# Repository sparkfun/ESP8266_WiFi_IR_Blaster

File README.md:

SparkFun WiFi IR Blaster (ESP8266)
========================================

[*SparkFun ESP8266 WiFi IR Blaster (DEV-15031)*](https://www.sparkfun.com/products/15031)

The WiFi IR Blaster is designed to connect all of your old, legacy IR-controlled devices to a WiFi network -- exposing them to a new method of control. Want to control your TV via a web-browser? Want to ask Alexa to mute your stereo? Want to schedule triggers to your IR-controlled LED strip? These are all applications that the WiFi IR Blaster is perfect for.

The WiFi IR Blaster combines an ESP8266 -- a powerful WiFi/microcontroller SoC -- with an IR emitter and receiver. With built-in WiFi support, the ESP8266 can be programmed to provide an interface between HTTP, MQTT, TCP, and UDP services and infrared-controlled devices.

This product includes the WiFi IR Blaster, a [Lite-ON LTE-302](https://www.sparkfun.com/datasheets/Components/LTE-302.pdf) infrared emitter, and a [TSOP38238 IR receiver](https://www.sparkfun.com/products/10266). The IR emitter and detector are not populated on the board -- allowing you to assemble them in any orientation your project requires.

For help getting started, check out our [WiFi IR Blaster Hookup Guide](https://learn.sparkfun.com/tutorials/wifi-ir-blaster-hookup-guide), which explains how to assemble the board, program it, and use the [IRremoteESP8266](https://github.com/markszabo/IRremoteESP8266) Arduino library.

SparkFun labored with love to create this code. Feel like supporting open source hardware? 
Buy a [breakout board](https://www.sparkfun.com/products/15000) from SparkFun!

Repository Contents
-------------------

* **/Documents** - Datasheets
* **/Hardware** - Eagle design files (.brd, .sch)
* **/Production** - Production panel files (.brd)

Documentation
--------------

* **[Hookup Guide](https://learn.sparkfun.com/tutorials/sparkfun-wifi-ir-blaster-hookup-guide)** - Basic hookup guide.

License Information
-------------------

This product is _**open source**_! 

If you have any questions or concerns on licensing, please contact techsupport@sparkfun.com.

Please use, reuse, and modify these files as you see fit. Please maintain attribution to SparkFun Electronics and release any derivative under the same license.

Distributed as-is; no warranty is given.

- Your friends at SparkFun.

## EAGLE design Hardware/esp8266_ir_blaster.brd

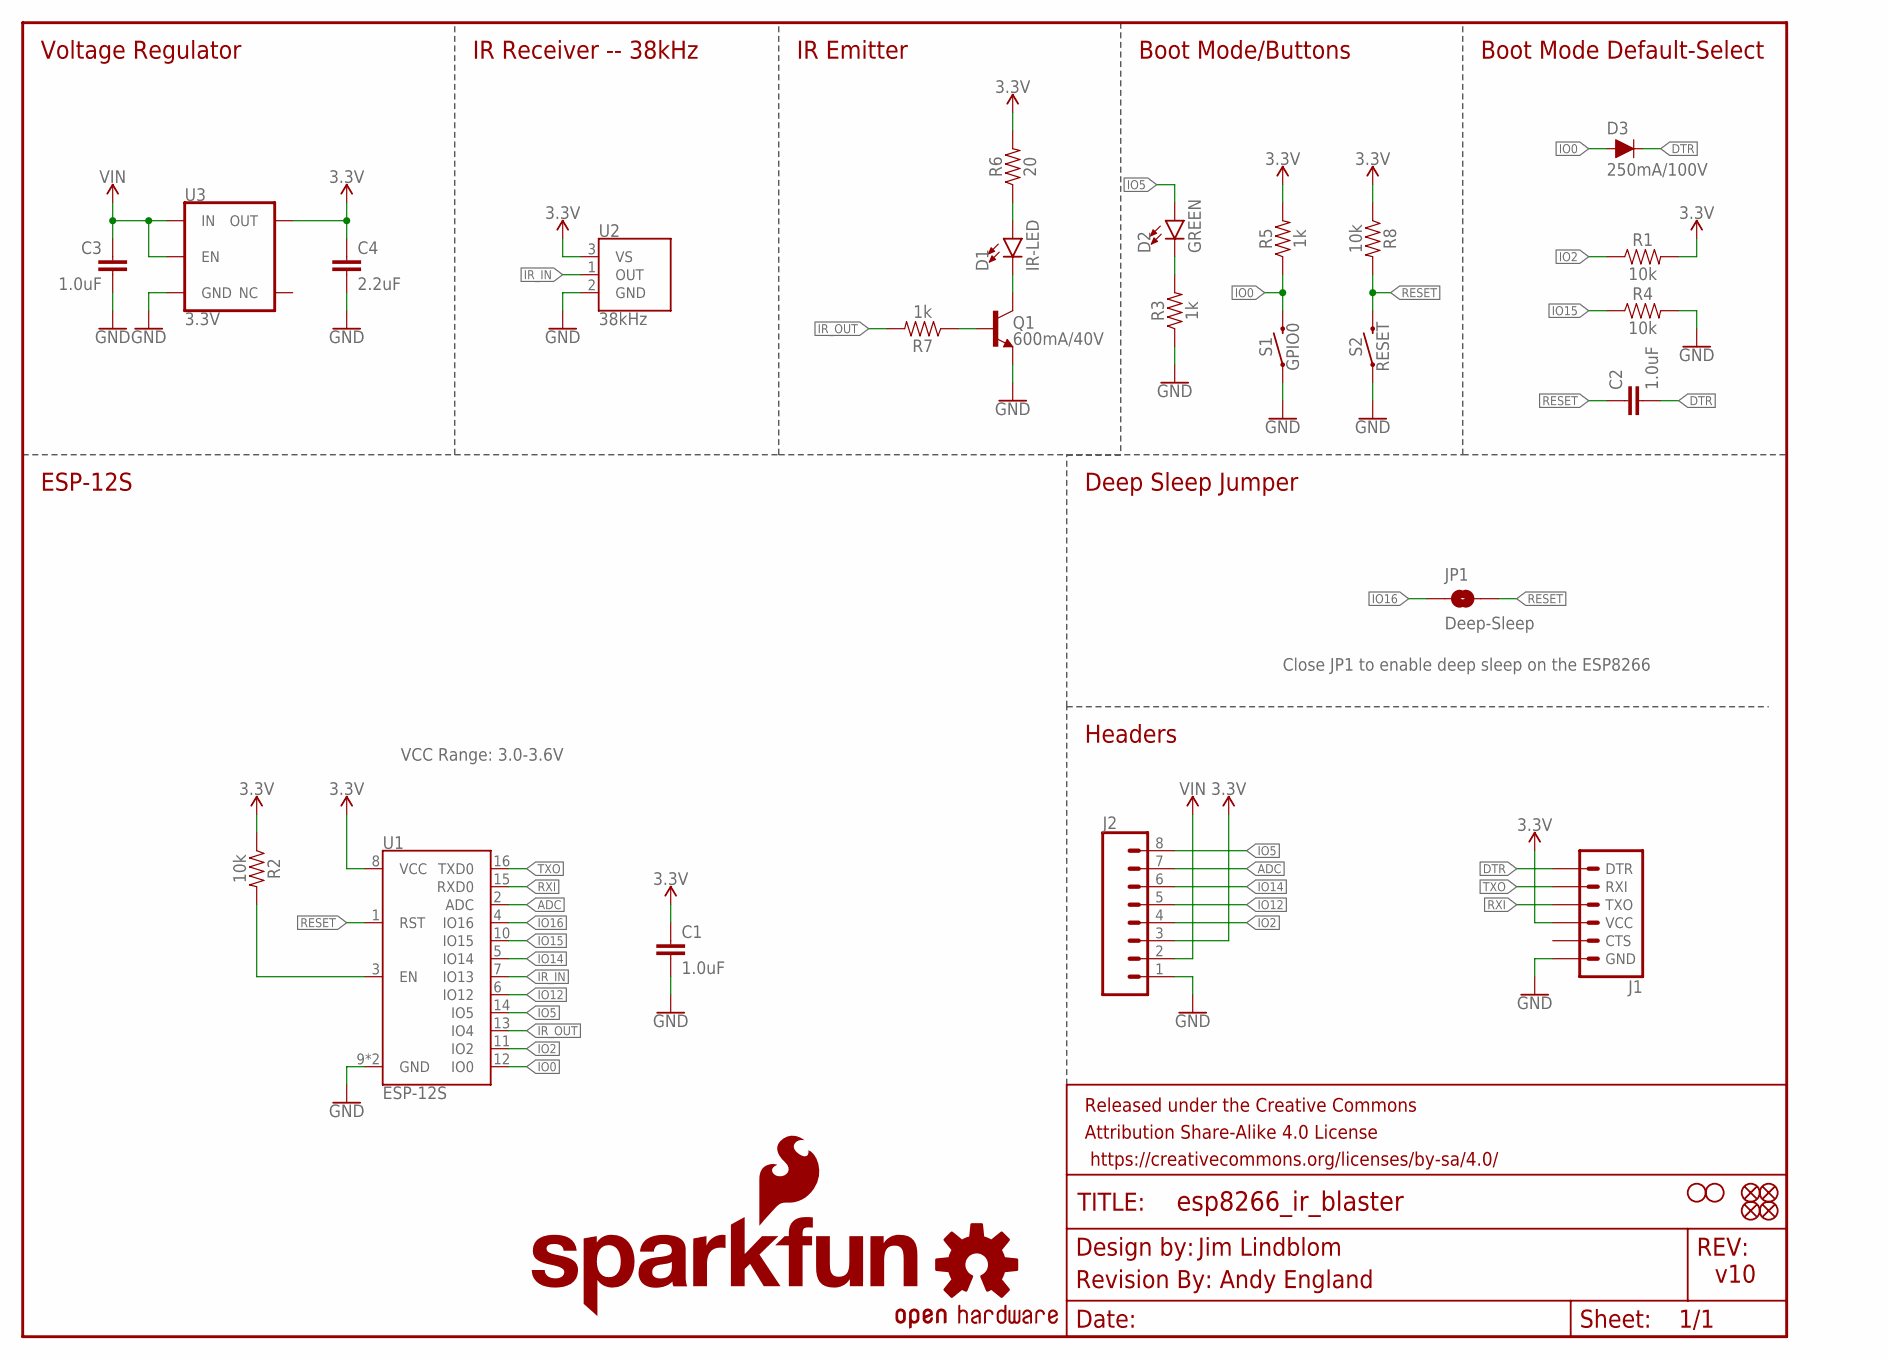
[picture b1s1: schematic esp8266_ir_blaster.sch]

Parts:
C1, C2, C3: 1.0uF; 0603
C4: 2.2uF; 0603
D1: IR-LED; LTE-302
D2: GREEN; LED-0603
D3: 250mA/100V; SOD-323
FD1, FD2, FD3, FD4: FIDUCIALUFIDUCIAL; FIDUCIAL-MICRO
FRAME1: FRAME-LETTER; CREATIVE_COMMONS
H1, H2: STAND-OFF
J1: 6_PIN_SERIAL_TARGETNO_SILK; 1X06_NO_SILK
J2: CONN_08NO_SILK_FEMALE_PTH; 1X08_NO_SILK
JP1: Deep-Sleep; SMT-JUMPER_2_NO_NO-SILK
LOGO1: OSHW-LOGOS; OSHW-LOGO-S
LOGO2: SFE_LOGO_NAME_FLAME.1_INCH; SFE_LOGO_NAME_FLAME_.1
LOGO3: REVISION
Q1: 600mA/40V; SOT23-3
R1, R2, R4, R8: 10k; 0603
R3, R5, R7: 1k; 0603
R6: 20; 0603
S1: GPIO0; TACTILE_SWITCH_SMD_4.6X2.8MM
S2: RESET; TACTILE_SWITCH_SMD_4.6X2.8MM
U1: ESP-12S
U2: 38kHz; TSOP382
U3: 3.3V; SOT23-5

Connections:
3.3V: C1.1, C4.1, J1.4 (VCC), J2.3, R1.2, R2.1, R5.2, R6.2, R8.1, U1.8 (VCC), U2.3 (VS), U3.5 (OUT)
ADC: J2.7, U1.2 (ADC)
CHIP_EN: R2.2, U1.3 (EN)
DTR: C2.2, D3.C, J1.1 (DTR)
GND: C1.2, C3.2, C4.2, J1.6 (GND), J2.1, Q1.2 (E), R3.1, R4.2, S1.1, S1.2 (1), S2.1, S2.2 (1), U1.9 (GND), U1.P$1 (GND), U2.2 (GND), U3.2 (GND)
IO0: D3.A, R5.1, S1.3 (2), S1.4 (2), U1.12 (IO0)
IO2: J2.4, R1.1, U1.11 (IO2)
IO5: D2.A, J2.8, U1.14 (IO5)
IO12: J2.5, U1.6 (IO12)
IO14: J2.6, U1.5 (IO14)
IO15: R4.1, U1.10 (IO15)
IO16: JP1.1, U1.4 (IO16)
IR_IN: U1.7 (IO13), U2.1 (OUT)
IR_OUT: R7.2, U1.13 (IO4)
unnamed: D2.C, R3.2
unnamed: D1.C, Q1.3 (C)
unnamed: D1.A, R6.1
unnamed: Q1.1 (B), R7.1
RESET: C2.1, JP1.2, R8.2, S2.3 (2), S2.4 (2), U1.1 (RST)
RXI: J1.3 (TXO), U1.15 (RXD0)
TXO: J1.2 (RXI), U1.16 (TXD0)
VIN: C3.1, J2.2, U3.1 (IN), U3.3 (EN)

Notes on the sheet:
Jim Lindblom
v10
IR Receiver -- 38kHz
IR Emitter
Boot Mode/Buttons
Boot Mode Default-Select
Deep Sleep Jumper
Headers
ESP-12S
Close JP1 to enable deep sleep on the ESP8266
VCC Range: 3.0-3.6V
Voltage Regulator
Andy England

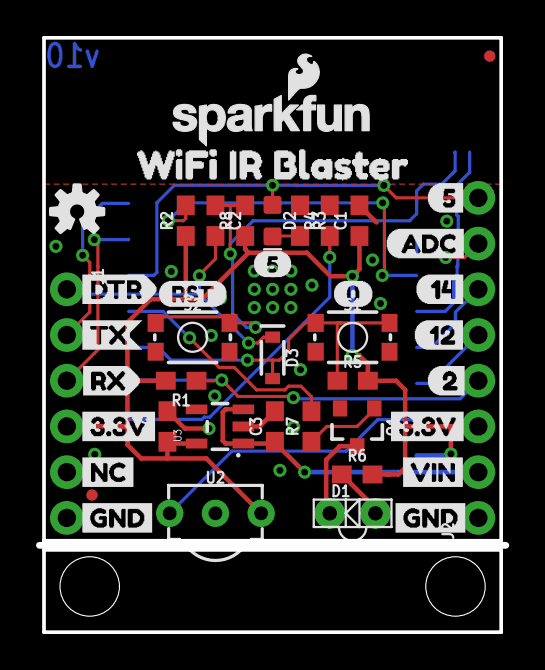
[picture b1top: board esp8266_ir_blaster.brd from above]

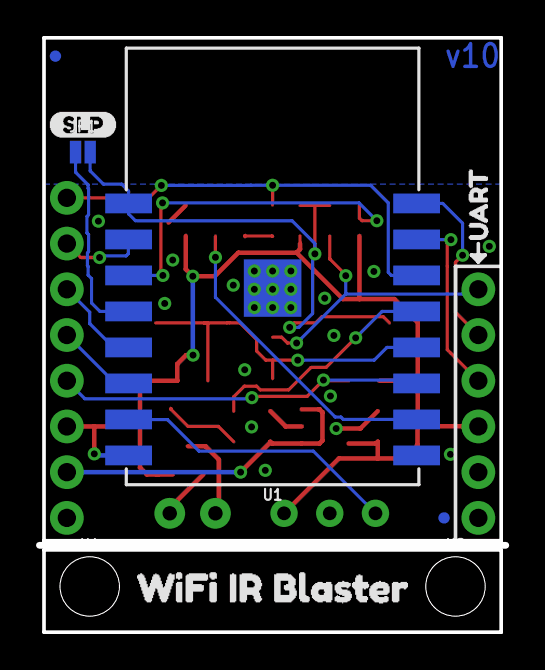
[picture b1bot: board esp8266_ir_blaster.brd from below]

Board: 2 copper layers, 25.9 x 32.8 mm, 55 parts (9 on the bottom side), 22 nets.

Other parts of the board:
U$1: 512
U$2, U$21: 3#3V4
U$3: SLP14
U$4, U$13: WIFI_IR_BLASTER11
U$5: UART0
U$6: DTR1
U$7: NC0
U$8: 511
U$9: ADC10
U$10: 129
U$11: 148
U$12: 27
U$14: 013
U$15: RST14
U$19: TX2
U$20: RX3
U$22, U$24: GND5
U$23: VIN6

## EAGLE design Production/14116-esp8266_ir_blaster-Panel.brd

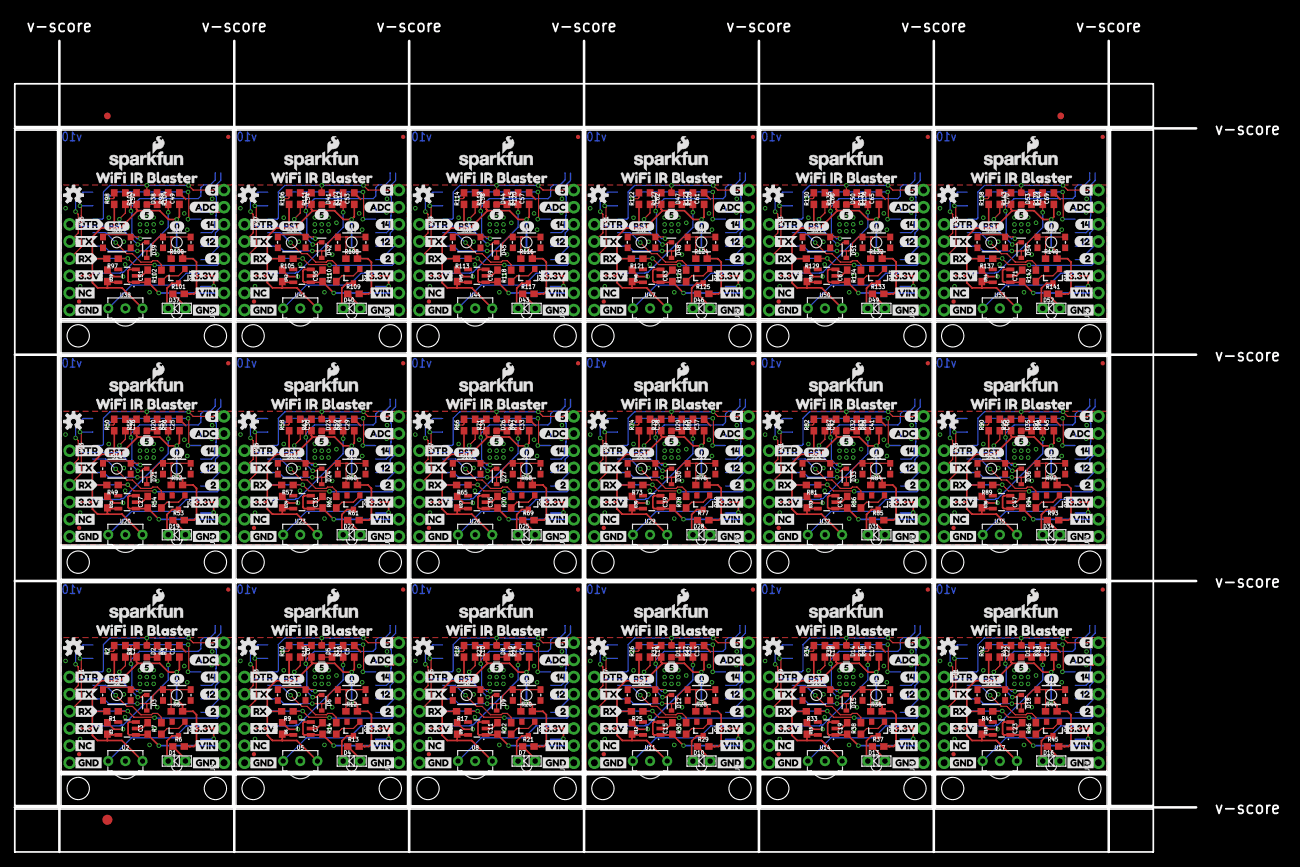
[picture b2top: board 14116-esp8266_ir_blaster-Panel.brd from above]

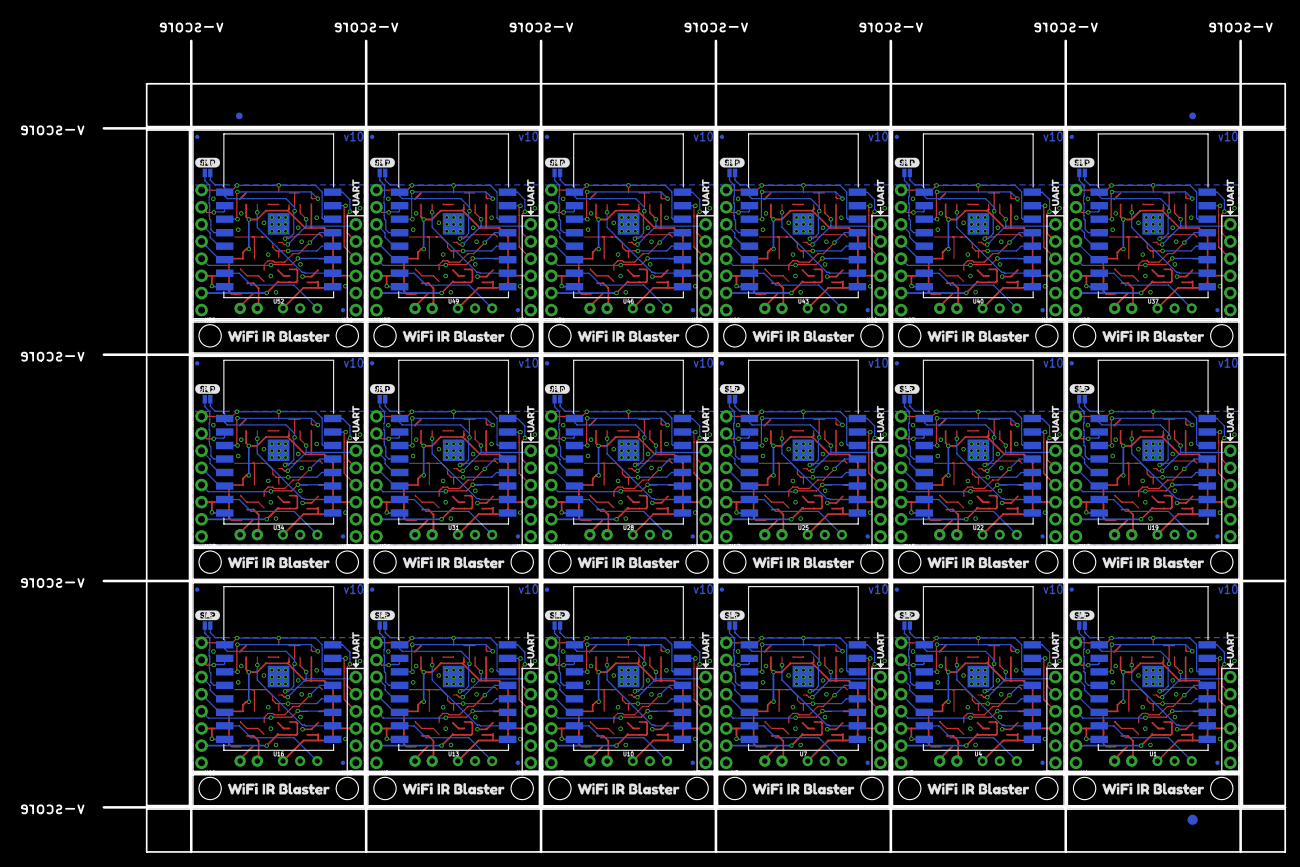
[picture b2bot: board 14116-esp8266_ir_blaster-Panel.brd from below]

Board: 2 copper layers, 188.2 x 124.0 mm, 960 parts (165 on the bottom side), 396 nets.

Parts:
C1, C2, C3, C5, C6, C7, C9, C10, C11, C13, C14, C15, C17, C18, C19, C21, C22, C23, C25, C26, C27, C29, C30, C31, C33, C34, C35, C37, C38, C39, C41, C42, C43, C45, C46, C47, C49, C50, C51, C53, C54, C55, C57, C58, C59, C61, C62, C63, C65, C66, C67, C69, C70, C71: 1.0uF; 0603
C4, C8, C12, C16, C20, C24, C28, C32, C36, C40, C44, C48, C52, C56, C60, C64, C68, C72: 2.2uF; 0603
D1, D4, D7, D10, D13, D16, D19, D22, D25, D28, D31, D34, D37, D40, D43, D46, D49, D52: IR-LED; LTE-302
D2, D5, D8, D11, D14, D17, D20, D23, D26, D29, D32, D35, D38, D41, D44, D47, D50, D53: GREEN; LED-0603
D3, D6, D9, D12, D15, D18, D21, D24, D27, D30, D33, D36, D39, D42, D45, D48, D51, D54: 250mA/100V; SOD-323
E$1, E$2, E$3, E$4: FIDUCIAL-1X2
E$5, E$6: FIDUCIAL-1.5X3
FD1, FD2, FD3, FD4, FD5, FD6, FD7, FD8, FD9, FD10, FD11, FD12, FD13, FD14, FD15, FD16, FD17, FD18, FD19, FD20, FD21, FD22, FD23, FD24, FD25, FD26, FD27, FD28, FD29, FD30, FD31, FD32, FD33, FD34, FD35, FD36, FD37, FD38, FD39, FD40, FD41, FD42, FD43, FD44, FD45, FD46, FD47, FD48, FD49, FD50, FD51, FD52, FD53, FD54, FD55, FD56, FD57, FD58, FD59, FD60, FD61, FD62, FD63, FD64, FD65, FD66, FD67, FD68, FD69, FD70, FD71, FD72: FIDUCIALUFIDUCIAL; FIDUCIAL-MICRO
H1, H2, H3, H4, H5, H6, H7, H8, H9, H10, H11, H12, H13, H14, H15, H16, H17, H18, H19, H20, H21, H22, H23, H24, H25, H26, H27, H28, H29, H30, H31, H32, H33, H34, H35, H36: STAND-OFF
J1, J3, J5, J7, J9, J11, J13, J15, J17, J19, J21, J23, J25, J27, J29, J31, J33, J35: 1X06_NO_SILK
J2, J4, J6, J8, J10, J12, J14, J16, J18, J20, J22, J24, J26, J28, J30, J32, J34, J36: 1X08_NO_SILK
JP1, JP2, JP3, JP4, JP5, JP6, JP7, JP8, JP9, JP10, JP11, JP12, JP13, JP14, JP15, JP16, JP17, JP18: Deep-Sleep; SMT-JUMPER_2_NO_NO-SILK
LOGO1, LOGO4, LOGO6, LOGO8, LOGO10, LOGO12, LOGO14, LOGO16, LOGO18, LOGO20, LOGO22, LOGO24, LOGO26, LOGO28, LOGO30, LOGO32, LOGO34, LOGO36: OSHW-LOGOS; OSHW-LOGO-S
LOGO2, LOGO3, LOGO5, LOGO7, LOGO9, LOGO11, LOGO13, LOGO15, LOGO17, LOGO19, LOGO21, LOGO23, LOGO25, LOGO27, LOGO29, LOGO31, LOGO33, LOGO35: SFE_LOGO_NAME_FLAME.1_INCH; SFE_LOGO_NAME_FLAME_.1
Q1, Q2, Q3, Q4, Q5, Q6, Q7, Q8, Q9, Q10, Q11, Q12, Q13, Q14, Q15, Q16, Q17, Q18: 600mA/40V; SOT23-3
R1, R2, R4, R8, R9, R10, R11, R15, R17, R18, R19, R23, R25, R26, R27, R31, R33, R34, R35, R39, R41, R42, R43, R47, R49, R50, R51, R55, R57, R58, R59, R63, R65, R66, R67, R71, R73, R74, R75, R79, R81, R82, R83, R87, R89, R90, R91, R95, R97, R98, R99, R103, R105, R106, R107, R111, R113, R114, R115, R119, R121, R122, R123, R127, R129, R130, R131, R135, R137, R138, R139, R143: 10k; 0603
R3, R5, R7, R12, R14, R16, R20, R22, R24, R28, R30, R32, R36, R38, R40, R44, R46, R48, R52, R54, R56, R60, R62, R64, R68, R70, R72, R76, R78, R80, R84, R86, R88, R92, R94, R96, R100, R102, R104, R108, R110, R112, R116, R118, R120, R124, R126, R128, R132, R134, R136, R140, R142, R144: 1k; 0603
R6, R13, R21, R29, R37, R45, R53, R61, R69, R77, R85, R93, R101, R109, R117, R125, R133, R141: 20; 0603
S1, S3, S5, S7, S9, S11, S13, S15, S17, S19, S21, S23, S25, S27, S29, S31, S33, S35: GPIO0; TACTILE_SWITCH_SMD_4.6X2.8MM
S2, S4, S6, S8, S10, S12, S14, S16, S18, S20, S22, S24, S26, S28, S30, S32, S34, S36: RESET; TACTILE_SWITCH_SMD_4.6X2.8MM
U1, U4, U7, U10, U13, U16, U19, U22, U25, U28, U31, U34, U37, U40, U43, U46, U49, U52: ESP-12S
U2, U5, U8, U11, U14, U17, U20, U23, U26, U29, U32, U35, U38, U41, U44, U47, U50, U53: 38kHz; TSOP382
U3, U6, U9, U12, U15, U18, U21, U24, U27, U30, U33, U36, U39, U42, U45, U48, U51, U54: 3.3V; SOT23-5
U$1, U$37, U$58, U$79, U$100, U$121, U$142, U$163, U$184, U$205, U$226, U$247, U$268, U$289, U$310, U$331, U$352, U$373: 512
U$2, U$21, U$28, U$38, U$49, U$59, U$70, U$80, U$91, U$101, U$112, U$122, U$133, U$143, U$154, U$164, U$175, U$185, U$196, U$206, U$217, U$227, U$238, U$248, U$259, U$269, U$280, U$290, U$301, U$311, U$322, U$332, U$343, U$353, U$364, U$374: 3#3V4
U$3, U$39, U$60, U$81, U$102, U$123, U$144, U$165, U$186, U$207, U$228, U$249, U$270, U$291, U$312, U$333, U$354, U$375: SLP14
U$4, U$13, U$16, U$40, U$43, U$61, U$64, U$82, U$85, U$103, U$106, U$124, U$127, U$145, U$148, U$166, U$169, U$187, U$190, U$208, U$211, U$229, U$232, U$250, U$253, U$271, U$274, U$292, U$295, U$313, U$316, U$334, U$337, U$355, U$358, U$376: WIFI_IR_BLASTER11
U$5, U$41, U$62, U$83, U$104, U$125, U$146, U$167, U$188, U$209, U$230, U$251, U$272, U$293, U$314, U$335, U$356, U$377: UART0
U$6, U$25, U$46, U$67, U$88, U$109, U$130, U$151, U$172, U$193, U$214, U$235, U$256, U$277, U$298, U$319, U$340, U$361: DTR1
U$7, U$42, U$63, U$84, U$105, U$126, U$147, U$168, U$189, U$210, U$231, U$252, U$273, U$294, U$315, U$336, U$357, U$378: NC0
U$8, U$30, U$51, U$72, U$93, U$114, U$135, U$156, U$177, U$198, U$219, U$240, U$261, U$282, U$303, U$324, U$345, U$366: 511
U$9, U$31, U$52, U$73, U$94, U$115, U$136, U$157, U$178, U$199, U$220, U$241, U$262, U$283, U$304, U$325, U$346, U$367: ADC10
U$10, U$32, U$53, U$74, U$95, U$116, U$137, U$158, U$179, U$200, U$221, U$242, U$263, U$284, U$305, U$326, U$347, U$368: 129
U$11, U$33, U$54, U$75, U$96, U$117, U$138, U$159, U$180, U$201, U$222, U$243, U$264, U$285, U$306, U$327, U$348, U$369: 148
U$12, U$34, U$55, U$76, U$97, U$118, U$139, U$160, U$181, U$202, U$223, U$244, U$265, U$286, U$307, U$328, U$349, U$370: 27
U$14, U$17, U$44, U$65, U$86, U$107, U$128, U$149, U$170, U$191, U$212, U$233, U$254, U$275, U$296, U$317, U$338, U$359: 013
U$15, U$18, U$45, U$66, U$87, U$108, U$129, U$150, U$171, U$192, U$213, U$234, U$255, U$276, U$297, U$318, U$339, U$360: RST14
U$19, U$26, U$47, U$68, U$89, U$110, U$131, U$152, U$173, U$194, U$215, U$236, U$257, U$278, U$299, U$320, U$341, U$362: TX2
U$20, U$27, U$48, U$69, U$90, U$111, U$132, U$153, U$174, U$195, U$216, U$237, U$258, U$279, U$300, U$321, U$342, U$363: RX3
U$22, U$24, U$29, U$36, U$50, U$57, U$71, U$78, U$92, U$99, U$113, U$120, U$134, U$141, U$155, U$162, U$176, U$183, U$197, U$204, U$218, U$225, U$239, U$246, U$260, U$267, U$281, U$288, U$302, U$309, U$323, U$330, U$344, U$351, U$365, U$372: GND5
U$23, U$35, U$56, U$77, U$98, U$119, U$140, U$161, U$182, U$203, U$224, U$245, U$266, U$287, U$308, U$329, U$350, U$371: VIN6

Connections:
3.3V: C1.1, C4.1, J1.4, J2.3, R1.2, R2.1, R5.2, R6.2, R8.1, U1.8, U2.3, U3.5
3.3V1: C5.1, C8.1, J3.4, J4.3, R9.2, R10.1, R12.2, R13.2, R15.1, U4.8, U5.3, U6.5
3.3V2: C9.1, C12.1, J5.4, J6.3, R17.2, R18.1, R20.2, R21.2, R23.1, U7.8, U8.3, U9.5
3.3V3: C13.1, C16.1, J7.4, J8.3, R25.2, R26.1, R28.2, R29.2, R31.1, U10.8, U11.3, U12.5
3.3V4: C17.1, C20.1, J9.4, J10.3, R33.2, R34.1, R36.2, R37.2, R39.1, U13.8, U14.3, U15.5
3.3V5: C21.1, C24.1, J11.4, J12.3, R41.2, R42.1, R44.2, R45.2, R47.1, U16.8, U17.3, U18.5
3.3V6: C25.1, C28.1, J13.4, J14.3, R49.2, R50.1, R52.2, R53.2, R55.1, U19.8, U20.3, U21.5
3.3V7: C29.1, C32.1, J15.4, J16.3, R57.2, R58.1, R60.2, R61.2, R63.1, U22.8, U23.3, U24.5
3.3V8: C33.1, C36.1, J17.4, J18.3, R65.2, R66.1, R68.2, R69.2, R71.1, U25.8, U26.3, U27.5
3.3V9: C37.1, C40.1, J19.4, J20.3, R73.2, R74.1, R76.2, R77.2, R79.1, U28.8, U29.3, U30.5
3.3V10: C41.1, C44.1, J21.4, J22.3, R81.2, R82.1, R84.2, R85.2, R87.1, U31.8, U32.3, U33.5
3.3V11: C45.1, C48.1, J23.4, J24.3, R89.2, R90.1, R92.2, R93.2, R95.1, U34.8, U35.3, U36.5
3.3V12: C49.1, C52.1, J25.4, J26.3, R97.2, R98.1, R100.2, R101.2, R103.1, U37.8, U38.3, U39.5
3.3V13: C53.1, C56.1, J27.4, J28.3, R105.2, R106.1, R108.2, R109.2, R111.1, U40.8, U41.3, U42.5
3.3V14: C57.1, C60.1, J29.4, J30.3, R113.2, R114.1, R116.2, R117.2, R119.1, U43.8, U44.3, U45.5
3.3V15: C61.1, C64.1, J31.4, J32.3, R121.2, R122.1, R124.2, R125.2, R127.1, U46.8, U47.3, U48.5
3.3V16: C65.1, C68.1, J33.4, J34.3, R129.2, R130.1, R132.2, R133.2, R135.1, U49.8, U50.3, U51.5
3.3V17: C69.1, C72.1, J35.4, J36.3, R137.2, R138.1, R140.2, R141.2, R143.1, U52.8, U53.3, U54.5
ADC: J2.7, U1.2
ADC1: J4.7, U4.2
ADC2: J6.7, U7.2
ADC3: J8.7, U10.2
ADC4: J10.7, U13.2
ADC5: J12.7, U16.2
ADC6: J14.7, U19.2
ADC7: J16.7, U22.2
ADC8: J18.7, U25.2
ADC9: J20.7, U28.2
ADC10: J22.7, U31.2
ADC11: J24.7, U34.2
ADC12: J26.7, U37.2
ADC13: J28.7, U40.2
ADC14: J30.7, U43.2
ADC15: J32.7, U46.2
ADC16: J34.7, U49.2
ADC17: J36.7, U52.2
CHIP_EN: R2.2, U1.3
CHIP_EN1: R10.2, U4.3
CHIP_EN2: R18.2, U7.3
CHIP_EN3: R26.2, U10.3
CHIP_EN4: R34.2, U13.3
CHIP_EN5: R42.2, U16.3
CHIP_EN6: R50.2, U19.3
CHIP_EN7: R58.2, U22.3
CHIP_EN8: R66.2, U25.3
CHIP_EN9: R74.2, U28.3
CHIP_EN10: R82.2, U31.3
CHIP_EN11: R90.2, U34.3
CHIP_EN12: R98.2, U37.3
CHIP_EN13: R106.2, U40.3
CHIP_EN14: R114.2, U43.3
CHIP_EN15: R122.2, U46.3
CHIP_EN16: R130.2, U49.3
CHIP_EN17: R138.2, U52.3
DTR: C2.2, D3.C, J1.1
DTR1: C6.2, D6.C, J3.1
DTR2: C10.2, D9.C, J5.1
DTR3: C14.2, D12.C, J7.1
DTR4: C18.2, D15.C, J9.1
DTR5: C22.2, D18.C, J11.1
DTR6: C26.2, D21.C, J13.1
DTR7: C30.2, D24.C, J15.1
DTR8: C34.2, D27.C, J17.1
DTR9: C38.2, D30.C, J19.1
DTR10: C42.2, D33.C, J21.1
DTR11: C46.2, D36.C, J23.1
DTR12: C50.2, D39.C, J25.1
DTR13: C54.2, D42.C, J27.1
DTR14: C58.2, D45.C, J29.1
DTR15: C62.2, D48.C, J31.1
DTR16: C66.2, D51.C, J33.1
DTR17: C70.2, D54.C, J35.1
GND: C1.2, C3.2, C4.2, J1.6, J2.1, Q1.2, R3.1, R4.2, S1.1, S1.2, S2.1, S2.2, U1.9, U1.P$1, U2.2, U3.2
GND1: C5.2, C7.2, C8.2, J3.6, J4.1, Q2.2, R11.2, R16.1, S3.1, S3.2, S4.1, S4.2, U4.9, U4.P$1, U5.2, U6.2
GND2: C9.2, C11.2, C12.2, J5.6, J6.1, Q3.2, R19.2, R24.1, S5.1, S5.2, S6.1, S6.2, U7.9, U7.P$1, U8.2, U9.2
GND3: C13.2, C15.2, C16.2, J7.6, J8.1, Q4.2, R27.2, R32.1, S7.1, S7.2, S8.1, S8.2, U10.9, U10.P$1, U11.2, U12.2
GND4: C17.2, C19.2, C20.2, J9.6, J10.1, Q5.2, R35.2, R40.1, S9.1, S9.2, S10.1, S10.2, U13.9, U13.P$1, U14.2, U15.2
GND5: C21.2, C23.2, C24.2, J11.6, J12.1, Q6.2, R43.2, R48.1, S11.1, S11.2, S12.1, S12.2, U16.9, U16.P$1, U17.2, U18.2
GND6: C25.2, C27.2, C28.2, J13.6, J14.1, Q7.2, R51.2, R56.1, S13.1, S13.2, S14.1, S14.2, U19.9, U19.P$1, U20.2, U21.2
GND7: C29.2, C31.2, C32.2, J15.6, J16.1, Q8.2, R59.2, R64.1, S15.1, S15.2, S16.1, S16.2, U22.9, U22.P$1, U23.2, U24.2
GND8: C33.2, C35.2, C36.2, J17.6, J18.1, Q9.2, R67.2, R72.1, S17.1, S17.2, S18.1, S18.2, U25.9, U25.P$1, U26.2, U27.2
GND9: C37.2, C39.2, C40.2, J19.6, J20.1, Q10.2, R75.2, R80.1, S19.1, S19.2, S20.1, S20.2, U28.9, U28.P$1, U29.2, U30.2
GND10: C41.2, C43.2, C44.2, J21.6, J22.1, Q11.2, R83.2, R88.1, S21.1, S21.2, S22.1, S22.2, U31.9, U31.P$1, U32.2, U33.2
GND11: C45.2, C47.2, C48.2, J23.6, J24.1, Q12.2, R91.2, R96.1, S23.1, S23.2, S24.1, S24.2, U34.9, U34.P$1, U35.2, U36.2
GND12: C49.2, C51.2, C52.2, J25.6, J26.1, Q13.2, R99.2, R104.1, S25.1, S25.2, S26.1, S26.2, U37.9, U37.P$1, U38.2, U39.2
GND13: C53.2, C55.2, C56.2, J27.6, J28.1, Q14.2, R107.2, R112.1, S27.1, S27.2, S28.1, S28.2, U40.9, U40.P$1, U41.2, U42.2
GND14: C57.2, C59.2, C60.2, J29.6, J30.1, Q15.2, R115.2, R120.1, S29.1, S29.2, S30.1, S30.2, U43.9, U43.P$1, U44.2, U45.2
GND15: C61.2, C63.2, C64.2, J31.6, J32.1, Q16.2, R123.2, R128.1, S31.1, S31.2, S32.1, S32.2, U46.9, U46.P$1, U47.2, U48.2
GND16: C65.2, C67.2, C68.2, J33.6, J34.1, Q17.2, R131.2, R136.1, S33.1, S33.2, S34.1, S34.2, U49.9, U49.P$1, U50.2, U51.2
GND17: C69.2, C71.2, C72.2, J35.6, J36.1, Q18.2, R139.2, R144.1, S35.1, S35.2, S36.1, S36.2, U52.9, U52.P$1, U53.2, U54.2
IO0: D3.A, R5.1, S1.3, S1.4, U1.12
IO1: R11.1, U4.10
IO2: J2.4, R1.1, U1.11
IO3: J4.4, R9.1, U4.11
IO4: D6.A, R12.1, S3.3, S3.4, U4.12
IO5: D2.A, J2.8, U1.14
IO6: J4.6, U4.5
IO7: JP2.1, U4.4
IO8: J4.5, U4.6
IO9: D5.A, J4.8, U4.14
IO10: R19.1, U7.10
IO11: J6.4, R17.1, U7.11
IO12: J2.5, U1.6
IO13: D9.A, R20.1, S5.3, S5.4, U7.12
IO14: J2.6, U1.5
IO15: R4.1, U1.10
IO16: JP1.1, U1.4
IO17: J6.6, U7.5
IO18: JP3.1, U7.4
IO19: J6.5, U7.6
IO20: D8.A, J6.8, U7.14
IO21: R27.1, U10.10
IO22: J8.4, R25.1, U10.11
IO23: D12.A, R28.1, S7.3, S7.4, U10.12
IO24: J8.6, U10.5
IO25: JP4.1, U10.4
IO26: J8.5, U10.6
IO27: D11.A, J8.8, U10.14
IO28: R35.1, U13.10
IO29: J10.4, R33.1, U13.11
IO30: D15.A, R36.1, S9.3, S9.4, U13.12
IO31: J10.6, U13.5
IO32: JP5.1, U13.4
IO33: J10.5, U13.6
IO34: D14.A, J10.8, U13.14
IO35: R43.1, U16.10
IO36: J12.4, R41.1, U16.11
IO37: D18.A, R44.1, S11.3, S11.4, U16.12
IO38: J12.6, U16.5
IO39: JP6.1, U16.4
IO40: J12.5, U16.6
IO41: D17.A, J12.8, U16.14
IO42: R51.1, U19.10
IO43: J14.4, R49.1, U19.11
IO44: D21.A, R52.1, S13.3, S13.4, U19.12
IO45: J14.6, U19.5
IO46: JP7.1, U19.4
IO47: J14.5, U19.6
IO48: D20.A, J14.8, U19.14
IO49: R59.1, U22.10
IO50: J16.4, R57.1, U22.11
IO51: D24.A, R60.1, S15.3, S15.4, U22.12
IO52: J16.6, U22.5
IO53: JP8.1, U22.4
IO54: J16.5, U22.6
IO55: D23.A, J16.8, U22.14
IO56: R67.1, U25.10
IO57: J18.4, R65.1, U25.11
IO58: D27.A, R68.1, S17.3, S17.4, U25.12
IO59: J18.6, U25.5
IO60: JP9.1, U25.4
IO61: J18.5, U25.6
IO62: D26.A, J18.8, U25.14
IO63: R75.1, U28.10
IO64: J20.4, R73.1, U28.11
IO65: D30.A, R76.1, S19.3, S19.4, U28.12
IO66: J20.6, U28.5
IO67: JP10.1, U28.4
IO68: J20.5, U28.6
IO69: D29.A, J20.8, U28.14
IO70: R83.1, U31.10
IO71: J22.4, R81.1, U31.11
IO72: D33.A, R84.1, S21.3, S21.4, U31.12
IO73: J22.6, U31.5
IO74: JP11.1, U31.4
IO75: J22.5, U31.6
IO76: D32.A, J22.8, U31.14
IO77: R91.1, U34.10
IO78: J24.4, R89.1, U34.11
IO79: D36.A, R92.1, S23.3, S23.4, U34.12
IO80: J24.6, U34.5
IO81: JP12.1, U34.4
IO82: J24.5, U34.6
IO83: D35.A, J24.8, U34.14
IO84: R99.1, U37.10
IO85: J26.4, R97.1, U37.11
IO86: D39.A, R100.1, S25.3, S25.4, U37.12
IO87: J26.6, U37.5
IO88: JP13.1, U37.4
IO89: J26.5, U37.6
IO90: D38.A, J26.8, U37.14
IO91: R107.1, U40.10
IO92: J28.4, R105.1, U40.11
IO93: D42.A, R108.1, S27.3, S27.4, U40.12
IO94: J28.6, U40.5
IO95: JP14.1, U40.4
IO96: J28.5, U40.6
IO97: D41.A, J28.8, U40.14
IO98: R115.1, U43.10
IO99: J30.4, R113.1, U43.11
IO100: D45.A, R116.1, S29.3, S29.4, U43.12
IO101: J30.6, U43.5
IO102: JP15.1, U43.4
IO103: J30.5, U43.6
IO104: D44.A, J30.8, U43.14
IO105: R123.1, U46.10
IO106: J32.4, R121.1, U46.11
IO107: D48.A, R124.1, S31.3, S31.4, U46.12
IO108: J32.6, U46.5
IO109: JP16.1, U46.4
IO110: J32.5, U46.6
IO111: D47.A, J32.8, U46.14
IO112: R131.1, U49.10
IO113: J34.4, R129.1, U49.11
IO114: D51.A, R132.1, S33.3, S33.4, U49.12
IO115: J34.6, U49.5
IO116: JP17.1, U49.4
IO117: J34.5, U49.6
IO118: D50.A, J34.8, U49.14
IO119: R139.1, U52.10
IO120: J36.4, R137.1, U52.11
IO121: D54.A, R140.1, S35.3, S35.4, U52.12
IO122: J36.6, U52.5
IO123: JP18.1, U52.4
IO124: J36.5, U52.6
IO125: D53.A, J36.8, U52.14
IR_IN: U1.7, U2.1
IR_IN1: U4.7, U5.1
IR_IN2: U7.7, U8.1
IR_IN3: U10.7, U11.1
IR_IN4: U13.7, U14.1
IR_IN5: U16.7, U17.1
IR_IN6: U19.7, U20.1
IR_IN7: U22.7, U23.1
IR_IN8: U25.7, U26.1
IR_IN9: U28.7, U29.1
IR_IN10: U31.7, U32.1
IR_IN11: U34.7, U35.1
IR_IN12: U37.7, U38.1
IR_IN13: U40.7, U41.1
IR_IN14: U43.7, U44.1
IR_IN15: U46.7, U47.1
IR_IN16: U49.7, U50.1
IR_IN17: U52.7, U53.1
IR_OUT: R7.2, U1.13
IR_OUT1: R14.2, U4.13
IR_OUT2: R22.2, U7.13
IR_OUT3: R30.2, U10.13
IR_OUT4: R38.2, U13.13
IR_OUT5: R46.2, U16.13
IR_OUT6: R54.2, U19.13
IR_OUT7: R62.2, U22.13
IR_OUT8: R70.2, U25.13
IR_OUT9: R78.2, U28.13
IR_OUT10: R86.2, U31.13
IR_OUT11: R94.2, U34.13
IR_OUT12: R102.2, U37.13
IR_OUT13: R110.2, U40.13
IR_OUT14: R118.2, U43.13
IR_OUT15: R126.2, U46.13
IR_OUT16: R134.2, U49.13
IR_OUT17: R142.2, U52.13
unnamed: D2.C, R3.2
unnamed: D4.C, Q2.3
unnamed: D4.A, R13.1
unnamed: Q2.1, R14.1
unnamed: D1.C, Q1.3
unnamed: D1.A, R6.1
unnamed: Q1.1, R7.1
unnamed: D5.C, R16.2
unnamed: D7.C, Q3.3
unnamed: D7.A, R21.1
unnamed: Q3.1, R22.1
unnamed: D8.C, R24.2
unnamed: D10.C, Q4.3
unnamed: D10.A, R29.1
unnamed: Q4.1, R30.1
unnamed: D11.C, R32.2
unnamed: D13.C, Q5.3
unnamed: D13.A, R37.1
unnamed: Q5.1, R38.1
unnamed: D14.C, R40.2
unnamed: D16.C, Q6.3
unnamed: D16.A, R45.1
unnamed: Q6.1, R46.1
unnamed: D17.C, R48.2
unnamed: D19.C, Q7.3
unnamed: D19.A, R53.1
unnamed: Q7.1, R54.1
unnamed: D20.C, R56.2
unnamed: D22.C, Q8.3
unnamed: D22.A, R61.1
unnamed: Q8.1, R62.1
unnamed: D23.C, R64.2
unnamed: D25.C, Q9.3
unnamed: D25.A, R69.1
unnamed: Q9.1, R70.1
unnamed: D26.C, R72.2
unnamed: D28.C, Q10.3
unnamed: D28.A, R77.1
unnamed: Q10.1, R78.1
unnamed: D29.C, R80.2
unnamed: D31.C, Q11.3
unnamed: D31.A, R85.1
unnamed: Q11.1, R86.1
unnamed: D32.C, R88.2
unnamed: D34.C, Q12.3
unnamed: D34.A, R93.1
unnamed: Q12.1, R94.1
unnamed: D35.C, R96.2
unnamed: D37.C, Q13.3
unnamed: D37.A, R101.1
unnamed: Q13.1, R102.1
unnamed: D38.C, R104.2
unnamed: D40.C, Q14.3
unnamed: D40.A, R109.1
unnamed: Q14.1, R110.1
unnamed: D41.C, R112.2
unnamed: D43.C, Q15.3
unnamed: D43.A, R117.1
unnamed: Q15.1, R118.1
unnamed: D44.C, R120.2
unnamed: D46.C, Q16.3
unnamed: D46.A, R125.1
unnamed: Q16.1, R126.1
unnamed: D47.C, R128.2
unnamed: D49.C, Q17.3
unnamed: D49.A, R133.1
unnamed: Q17.1, R134.1
unnamed: D50.C, R136.2
unnamed: D52.C, Q18.3
unnamed: D52.A, R141.1
unnamed: Q18.1, R142.1
unnamed: D53.C, R144.2
RESET: C2.1, JP1.2, R8.2, S2.3, S2.4, U1.1
RESET1: C6.1, JP2.2, R15.2, S4.3, S4.4, U4.1
RESET2: C10.1, JP3.2, R23.2, S6.3, S6.4, U7.1
RESET3: C14.1, JP4.2, R31.2, S8.3, S8.4, U10.1
RESET4: C18.1, JP5.2, R39.2, S10.3, S10.4, U13.1
RESET5: C22.1, JP6.2, R47.2, S12.3, S12.4, U16.1
RESET6: C26.1, JP7.2, R55.2, S14.3, S14.4, U19.1
RESET7: C30.1, JP8.2, R63.2, S16.3, S16.4, U22.1
RESET8: C34.1, JP9.2, R71.2, S18.3, S18.4, U25.1
RESET9: C38.1, JP10.2, R79.2, S20.3, S20.4, U28.1
RESET10: C42.1, JP11.2, R87.2, S22.3, S22.4, U31.1
RESET11: C46.1, JP12.2, R95.2, S24.3, S24.4, U34.1
RESET12: C50.1, JP13.2, R103.2, S26.3, S26.4, U37.1
RESET13: C54.1, JP14.2, R111.2, S28.3, S28.4, U40.1
RESET14: C58.1, JP15.2, R119.2, S30.3, S30.4, U43.1
RESET15: C62.1, JP16.2, R127.2, S32.3, S32.4, U46.1
RESET16: C66.1, JP17.2, R135.2, S34.3, S34.4, U49.1
RESET17: C70.1, JP18.2, R143.2, S36.3, S36.4, U52.1
RXI: J1.3, U1.15
RXI1: J3.3, U4.15
RXI2: J5.3, U7.15
RXI3: J7.3, U10.15
RXI4: J9.3, U13.15
RXI5: J11.3, U16.15
RXI6: J13.3, U19.15
RXI7: J15.3, U22.15
RXI8: J17.3, U25.15
RXI9: J19.3, U28.15
RXI10: J21.3, U31.15
RXI11: J23.3, U34.15
RXI12: J25.3, U37.15
RXI13: J27.3, U40.15
RXI14: J29.3, U43.15
RXI15: J31.3, U46.15
RXI16: J33.3, U49.15
RXI17: J35.3, U52.15
TXO: J1.2, U1.16
TXO1: J3.2, U4.16
TXO2: J5.2, U7.16
TXO3: J7.2, U10.16
TXO4: J9.2, U13.16
TXO5: J11.2, U16.16
TXO6: J13.2, U19.16
TXO7: J15.2, U22.16
TXO8: J17.2, U25.16
TXO9: J19.2, U28.16
TXO10: J21.2, U31.16
TXO11: J23.2, U34.16
TXO12: J25.2, U37.16
TXO13: J27.2, U40.16
TXO14: J29.2, U43.16
TXO15: J31.2, U46.16
TXO16: J33.2, U49.16
TXO17: J35.2, U52.16
VIN: C3.1, J2.2, U3.1, U3.3
VIN1: C7.1, J4.2, U6.1, U6.3
VIN2: C11.1, J6.2, U9.1, U9.3
VIN3: C15.1, J8.2, U12.1, U12.3
VIN4: C19.1, J10.2, U15.1, U15.3
VIN5: C23.1, J12.2, U18.1, U18.3
VIN6: C27.1, J14.2, U21.1, U21.3
VIN7: C31.1, J16.2, U24.1, U24.3
VIN8: C35.1, J18.2, U27.1, U27.3
VIN9: C39.1, J20.2, U30.1, U30.3
VIN10: C43.1, J22.2, U33.1, U33.3
VIN11: C47.1, J24.2, U36.1, U36.3
VIN12: C51.1, J26.2, U39.1, U39.3
VIN13: C55.1, J28.2, U42.1, U42.3
VIN14: C59.1, J30.2, U45.1, U45.3
VIN15: C63.1, J32.2, U48.1, U48.3
VIN16: C67.1, J34.2, U51.1, U51.3
VIN17: C71.1, J36.2, U54.1, U54.3

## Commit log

2018-09-27 Adding thermal pad
2018-09-28 updating to reds
2018-10-01 post checklist changes
2018-10-02 adding vin ranges
2018-10-03 panel v10 created

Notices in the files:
parts and their libraries:
SparkFun-Aesthetics: Licensing: Creative Commons ShareAlike 4.0 International - https://creativecommons.org/licenses/by-sa/4.0
SparkFun-Aesthetics: Released under the Creative Commons Attribution Share-Alike 4.0 License
SparkFun-Aesthetics: https://creativecommons.org/licenses/by-sa/4.0
